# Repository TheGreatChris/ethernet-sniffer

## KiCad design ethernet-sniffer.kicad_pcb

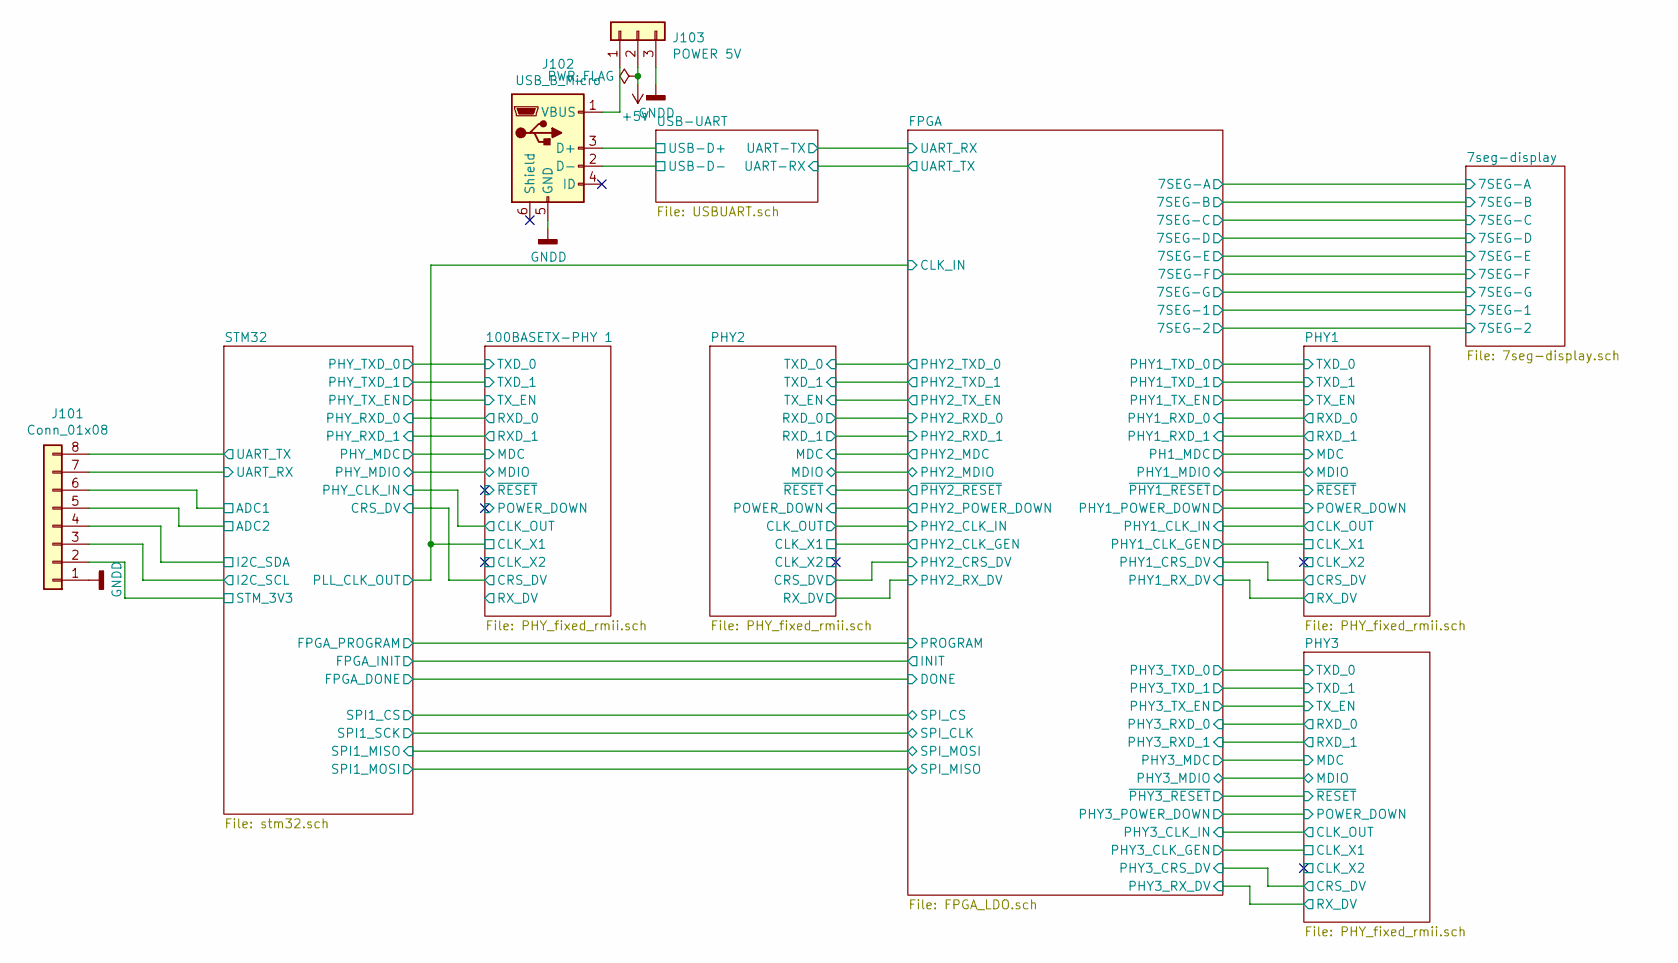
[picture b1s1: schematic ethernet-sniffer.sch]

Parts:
J101: Conn_01x08; PinHeader_1x08_P2.54mm_Vertical
J102: USB_B_Micro; USB_Micro-B_Amphenol_10103594-0001LF_Horizontal
J103: POWER 5V; PinHeader_1x03_P2.54mm_Vertical

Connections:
+5V: J103.2; also elsewhere on the board
/STM32/ADC1: J101.6; also elsewhere on the board
/STM32/ADC2: J101.5; also elsewhere on the board
/STM32/I2C_SCL: J101.3; also elsewhere on the board
/STM32/I2C_SDA: J101.4; also elsewhere on the board
/STM32/STM_3V3: J101.2; also elsewhere on the board
/STM32/UART_RX: J101.7; also elsewhere on the board
/STM32/UART_TX: J101.8; also elsewhere on the board
/USB-UART/USB-D+: J102.3 (D+); also elsewhere on the board
/USB-UART/USB-D-: J102.2 (D-); also elsewhere on the board
GNDD: J101.1, J102.5 (GND), J103.3; also elsewhere on the board
unnamed: J102.1 (VBUS), J103.1

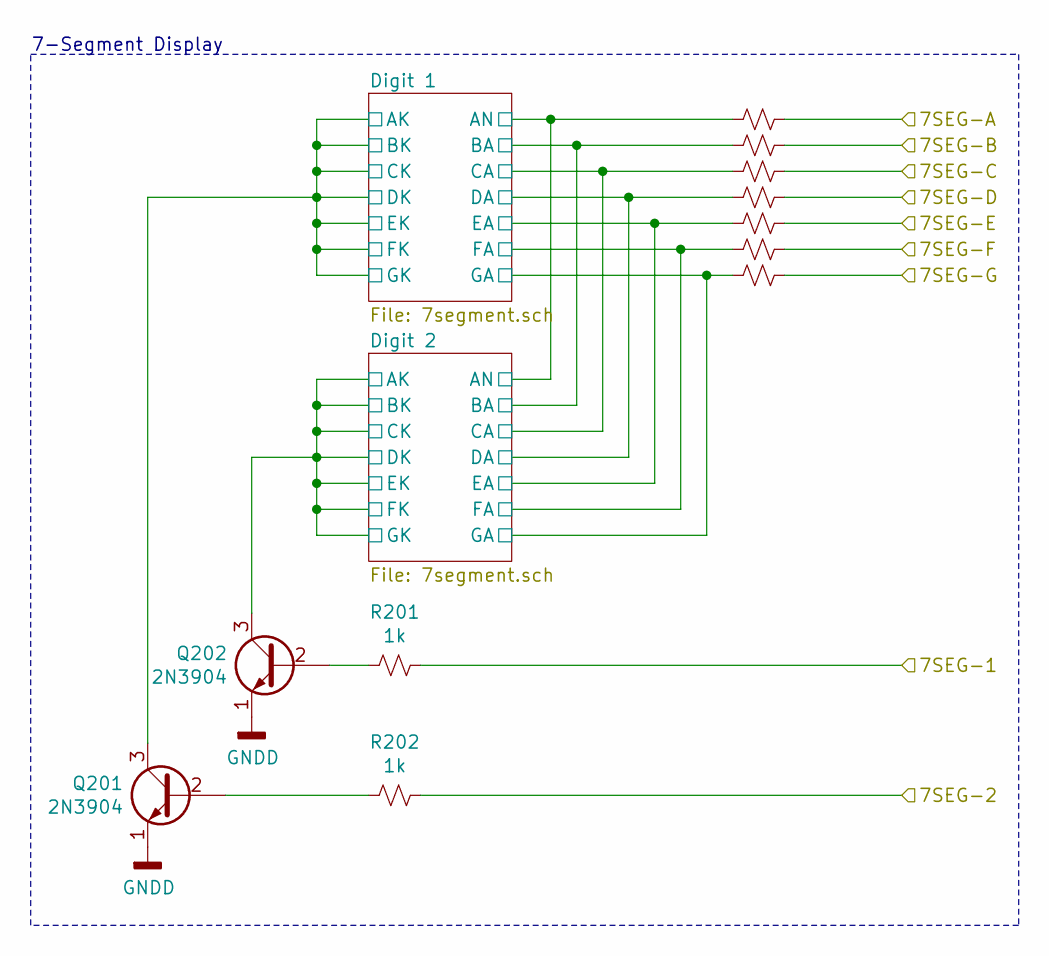
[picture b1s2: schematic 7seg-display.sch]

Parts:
Q201, Q202: 2N3904; SOT-23
R201, R202: 1k; R_0402_1005Metric
R203, R204, R205, R206, R207, R208, R209: 200; R_0402_1005Metric

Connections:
/7seg-display/7SEG-1: R201.1; also elsewhere on the board
/7seg-display/7SEG-2: R202.1; also elsewhere on the board
/7seg-display/7SEG-A: R203.1; also elsewhere on the board
/7seg-display/7SEG-B: R204.1; also elsewhere on the board
/7seg-display/7SEG-C: R205.1; also elsewhere on the board
/7seg-display/7SEG-D: R206.1; also elsewhere on the board
/7seg-display/7SEG-E: R207.1; also elsewhere on the board
/7seg-display/7SEG-F: R208.1; also elsewhere on the board
/7seg-display/7SEG-G: R209.1; also elsewhere on the board
/7seg-display/Digit 1/AK: Q201.3 (C); also elsewhere on the board
/7seg-display/Digit 1/AN: R203.2; also elsewhere on the board
/7seg-display/Digit 1/BA: R204.2; also elsewhere on the board
/7seg-display/Digit 1/CA: R205.2; also elsewhere on the board
/7seg-display/Digit 1/DA: R206.2; also elsewhere on the board
/7seg-display/Digit 1/EA: R207.2; also elsewhere on the board
/7seg-display/Digit 1/FA: R208.2; also elsewhere on the board
/7seg-display/Digit 1/GA: R209.2; also elsewhere on the board
/7seg-display/Digit 2/AK: Q202.3 (C); also elsewhere on the board
GNDD: Q201.1 (E), Q202.1 (E); also elsewhere on the board
unnamed: Q201.2 (B), R202.2
unnamed: Q202.2 (B), R201.2

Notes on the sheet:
7-Segment Display

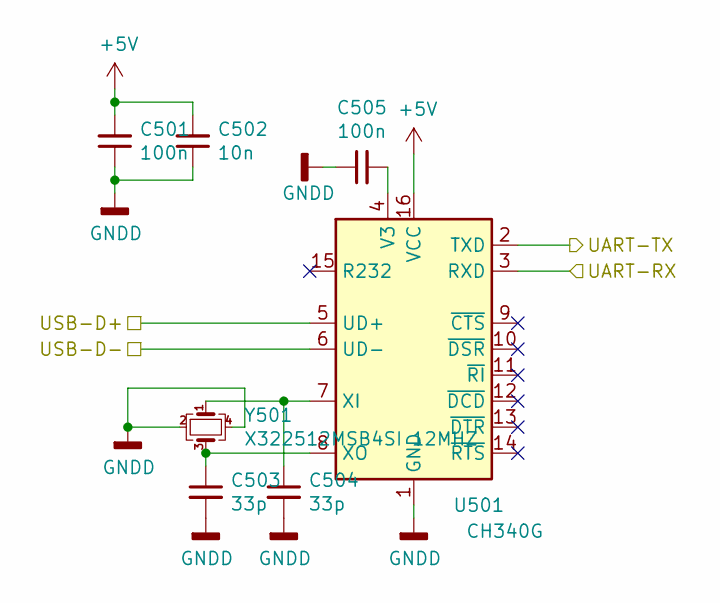
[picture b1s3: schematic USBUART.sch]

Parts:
C501, C505: 100n; C_0402_1005Metric
C502: 10n; C_0402_1005Metric
C503, C504: 33p; C_0402_1005Metric
U501: CH340G; SOIC-16_3.9x9.9mm_P1.27mm
Y501: X322512MSB4SI 12MHZ; Crystal_SMD_3225-4Pin_3.2x2.5mm

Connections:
+5V: C501.2, C502.2, U501.16 (VCC); also elsewhere on the board
/USB-UART/UART-RX: U501.3 (RXD); also elsewhere on the board
/USB-UART/UART-TX: U501.2 (TXD); also elsewhere on the board
/USB-UART/USB-D+: U501.5 (UD+); also elsewhere on the board
/USB-UART/USB-D-: U501.6 (UD-); also elsewhere on the board
GNDD: C501.1, C502.1, C503.2, C504.2, C505.1, U501.1 (GND), Y501.2, Y501.4; also elsewhere on the board
unnamed: C503.1, U501.8 (XO), Y501.3
unnamed: C504.1, U501.7 (XI), Y501.1
unnamed: C505.2, U501.4 (V3)

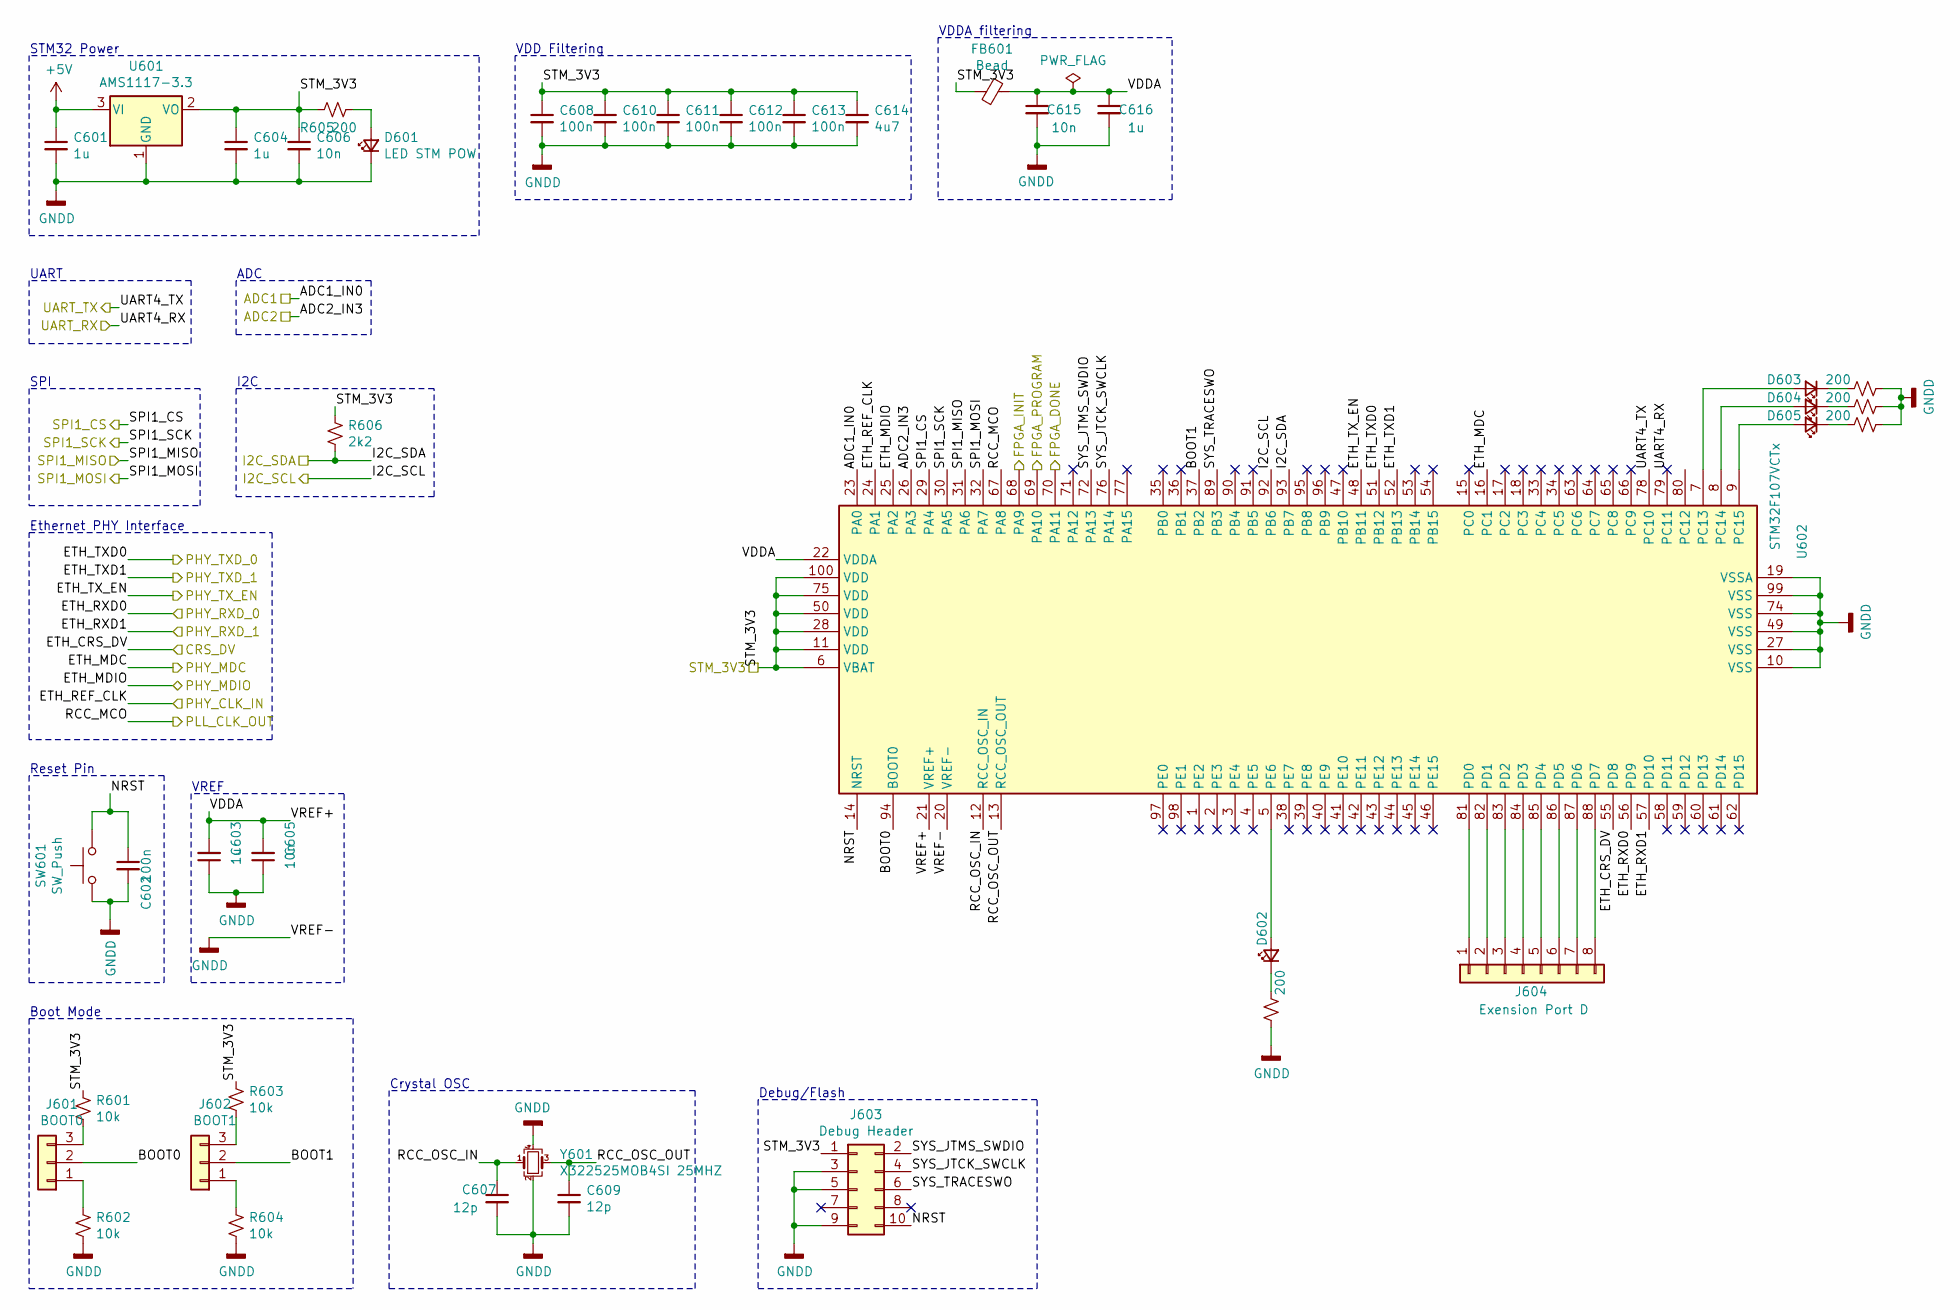
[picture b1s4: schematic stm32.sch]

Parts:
C601, C603, C604, C616: 1u; C_0402_1005Metric
C602, C608, C610, C611, C612, C613: 100n; C_0402_1005Metric
C605, C606, C615: 10n; C_0402_1005Metric
C607, C609: 12p; C_0402_1005Metric
C614: 4u7; C_0402_1005Metric
D601: LED STM POW; LED_0603_1608Metric
D602, D603, D604, D605: LED_Small; LED_0603_1608Metric
FB601: Bead; L_0805_2012Metric
J601: BOOT0; PinHeader_1x03_P2.54mm_Vertical
J602: BOOT1; PinHeader_1x03_P2.54mm_Vertical
J603: Debug Header; PinHeader_2x05_P2.54mm_Vertical
J604: Exension Port D; PinHeader_1x08_P2.54mm_Vertical
R601, R602, R603, R604: 10k; R_0402_1005Metric
R605, R607, R608, R609, R610: 200; R_0402_1005Metric
R606: 2k2; R_0402_1005Metric
SW601: SW_Push; SW_Push_SPST_NO_Alps_SKRK
U601: AMS1117-3.3; SOT-223-3_TabPin2
U602: STM32F107VCTx; LQFP-100_14x14mm_P0.5mm
Y601: X322525MOB4SI 25MHZ; Crystal_SMD_3225-4Pin_3.2x2.5mm

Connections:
+5V: C601.1, U601.3 (VI); also elsewhere on the board
/100BASETX-PHY 1/CLK_OUT: U602.24 (PA1); also elsewhere on the board
/100BASETX-PHY 1/CRS_DV: U602.55 (PD8); also elsewhere on the board
/100BASETX-PHY 1/MDC: U602.16 (PC1); also elsewhere on the board
/100BASETX-PHY 1/MDIO: U602.25 (PA2); also elsewhere on the board
/FPGA/CLK_IN: U602.67 (PA8); also elsewhere on the board
/FPGA/DONE: U602.70 (PA11); also elsewhere on the board
/STM32/ADC1: U602.23 (PA0); also elsewhere on the board
/STM32/ADC2: U602.26 (PA3); also elsewhere on the board
/STM32/BOOT0: J601.2, U602.94 (BOOT0)
/STM32/BOOT1: J602.2, U602.37 (PB2)
/STM32/FPGA_INIT: U602.68 (PA9); also elsewhere on the board
/STM32/FPGA_PROGRAM: U602.69 (PA10); also elsewhere on the board
/STM32/I2C_SCL: U602.92 (PB6); also elsewhere on the board
/STM32/I2C_SDA: R606.2, U602.93 (PB7); also elsewhere on the board
/STM32/NRST: C602.1, J603.10, SW601.2, U602.14 (NRST)
/STM32/PHY_RXD_0: U602.56 (PD9); also elsewhere on the board
/STM32/PHY_RXD_1: U602.57 (PD10); also elsewhere on the board
/STM32/PHY_TXD_0: U602.51 (PB12); also elsewhere on the board
/STM32/PHY_TXD_1: U602.52 (PB13); also elsewhere on the board
/STM32/PHY_TX_EN: U602.48 (PB11); also elsewhere on the board
/STM32/RCC_OSC_IN: C607.1, U602.12 (RCC_OSC_IN), Y601.1
/STM32/RCC_OSC_OUT: C609.1, U602.13 (RCC_OSC_OUT), Y601.3
/STM32/SPI1_CS: U602.29 (PA4); also elsewhere on the board
/STM32/SPI1_MISO: U602.31 (PA6); also elsewhere on the board
/STM32/SPI1_MOSI: U602.32 (PA7); also elsewhere on the board
/STM32/SPI1_SCK: U602.30 (PA5); also elsewhere on the board
/STM32/STM_3V3: C604.1, C606.1, C608.1, C610.1, C611.1, C612.1, C613.1, C614.1, FB601.2, J603.1, R601.1, R603.1, R605.1, R606.1, U601.2 (VO), U602.6 (VBAT), U602.11 (VDD), U602.28 (VDD), U602.50 (VDD), U602.75 (VDD), U602.100 (VDD); also elsewhere on the board
/STM32/SYS_JTCK_SWCLK: J603.4, U602.76 (PA14)
/STM32/SYS_JTMS_SWDIO: J603.2, U602.72 (PA13)
/STM32/SYS_TRACESWO: J603.6, U602.89 (PB3)
/STM32/UART_RX: U602.79 (PC11); also elsewhere on the board
/STM32/UART_TX: U602.78 (PC10); also elsewhere on the board
/STM32/VDDA: C603.2, C605.2, C615.1, C616.1, FB601.1, U602.21 (VREF+), U602.22 (VDDA)
GNDD: C601.2, C602.2, C603.1, C604.2, C605.1, C606.2, C607.2, C608.2, C609.2, C610.2, C611.2, C612.2, C613.2, C614.2, C615.2, C616.2, D601.1 (K), J603.3, J603.5, J603.9, R602.2, R604.2, R607.1, R608.1, R609.1, R610.1, SW601.1, U601.1 (GND), U602.10 (VSS), U602.19 (VSSA), U602.20 (VREF-), U602.27 (VSS), U602.49 (VSS), U602.74 (VSS), U602.99 (VSS), Y601.2, Y601.4; also elsewhere on the board
unnamed: D601.2 (A), R605.2
unnamed: D602.1 (K), R607.2
unnamed: D602.2 (A), U602.5 (PE6)
unnamed: D603.1 (K), R608.2
unnamed: D603.2 (A), U602.7 (PC13)
unnamed: D604.1 (K), R609.2
unnamed: D604.2 (A), U602.8 (PC14)
unnamed: D605.1 (K), R610.2
unnamed: D605.2 (A), U602.9 (PC15)
unnamed: J601.1, R602.1
unnamed: J601.3, R601.2
unnamed: J602.1, R604.1
unnamed: J602.3, R603.2
unnamed: J604.1, U602.81 (PD0)
unnamed: J604.2, U602.82 (PD1)
unnamed: J604.3, U602.83 (PD2)
unnamed: J604.4, U602.84 (PD3)
unnamed: J604.5, U602.85 (PD4)
unnamed: J604.6, U602.86 (PD5)
unnamed: J604.7, U602.87 (PD6)
unnamed: J604.8, U602.88 (PD7)

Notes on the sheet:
Reset Pin
Boot Mode
VREF
Crystal OSC
Debug/Flash
Ethernet PHY Interface
SPI
STM32 Power
VDD Filtering
UART
ADC
VDDA filtering
I2C

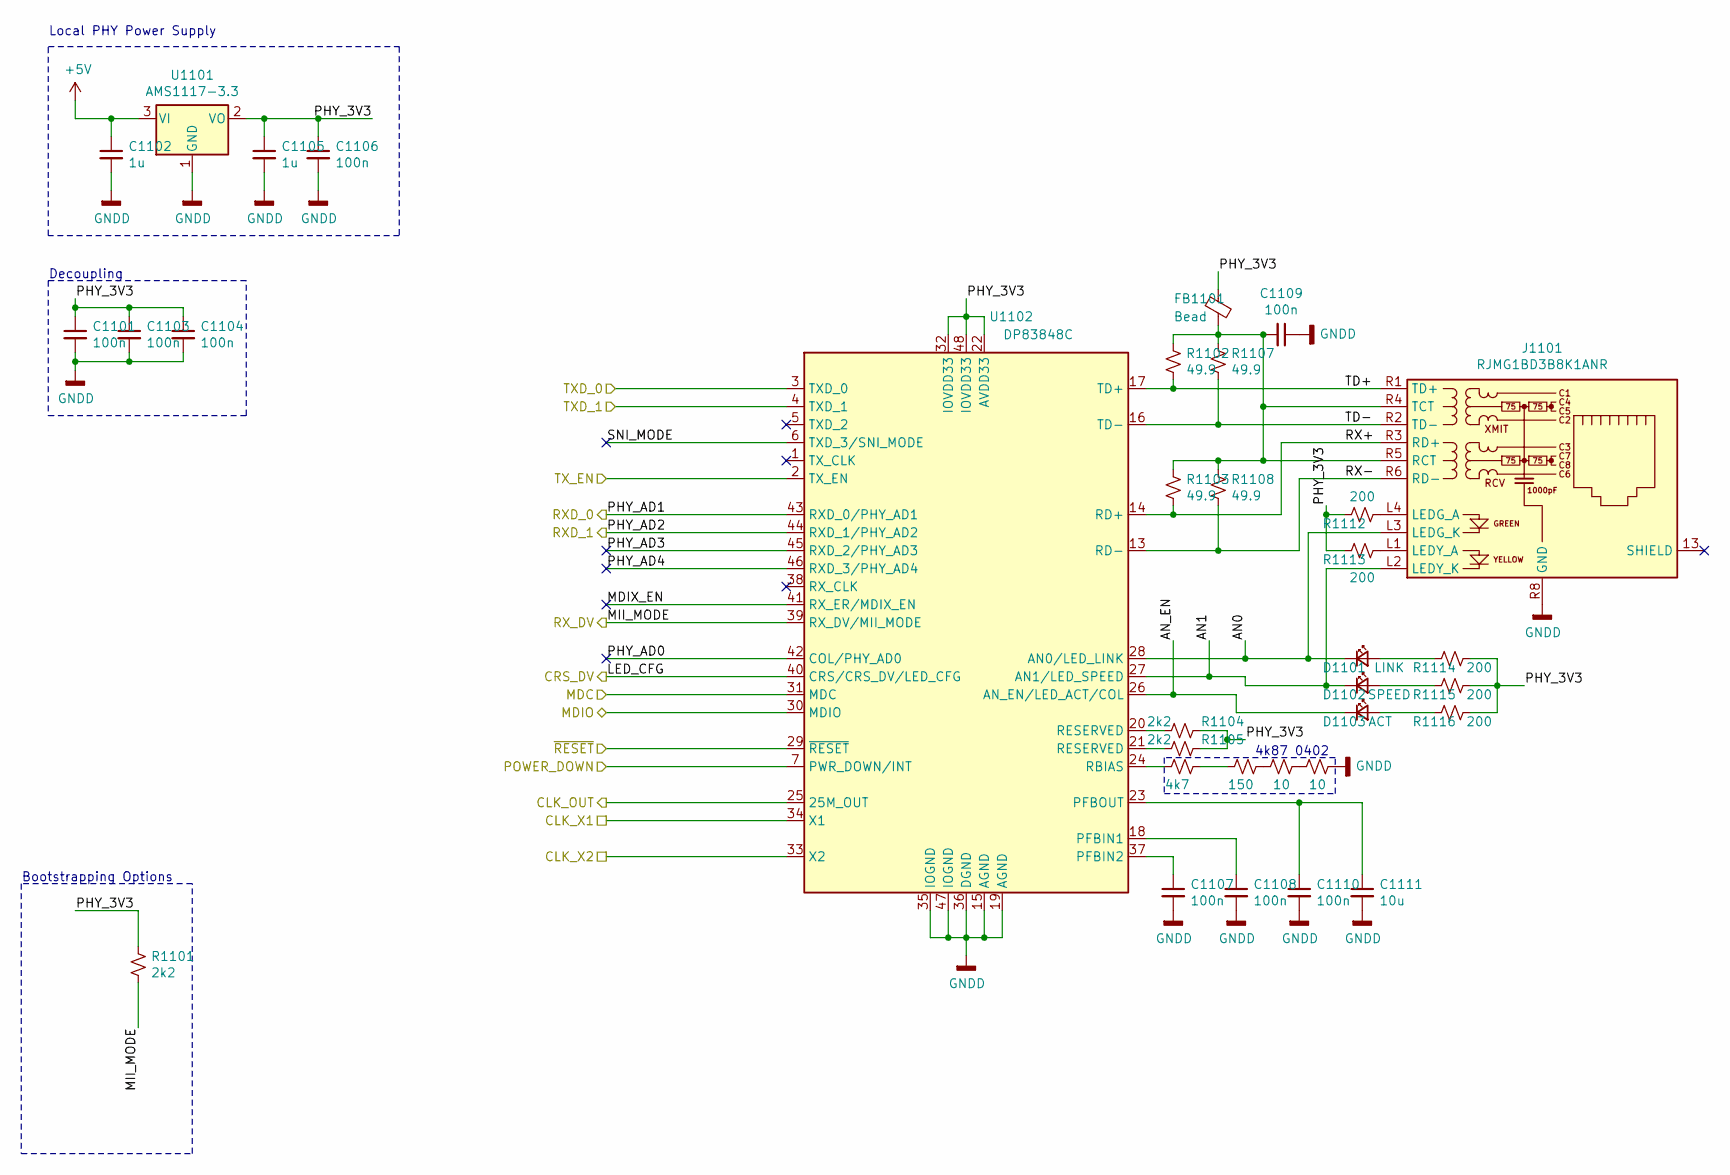
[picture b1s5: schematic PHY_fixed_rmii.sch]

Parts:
C702, C705: 1u; C_0402_1005Metric
C706, C707, C708, C709, C710, C1001, C1003, C1004: 100n; C_0402_1005Metric
C711: 10u; C_0402_1005Metric
D701: LINK; LED_0603_1608Metric
D702: SPEED; LED_0603_1608Metric
D703: ACT; LED_0603_1608Metric
FB701: Bead; L_0805_2012Metric
J701: RJMG1BD3B8K1ANR; RJ45_Amphenol_RJMG1BD3B8K1ANR
R701, R704, R705: 2k2; R_0402_1005Metric
R702, R703, R707, R708: 49.9; R_0402_1005Metric
R706: 4k7; R_0402_1005Metric
R709: 150; R_0402_1005Metric
R710, R711: 10; R_0402_1005Metric
R712, R713, R714, R715, R716: 200; R_0402_1005Metric
U701: AMS1117-3.3; SOT-223-3_TabPin2
U702: DP83848C; LQFP-48_7x7mm_P0.5mm

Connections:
+5V: C702.1, U701.3 (VI); also elsewhere on the board
/100BASETX-PHY 1/AN0: D701.1 (K), J701.L3 (LEDG_K), U702.28 (AN0/LED_LINK)
/100BASETX-PHY 1/AN1: D702.1 (K), J701.L2 (LEDY_K), U702.27 (AN1/LED_SPEED)
/100BASETX-PHY 1/AN_EN: D703.1 (K), U702.26 (AN_EN/LED_ACT/COL)
/100BASETX-PHY 1/CLK_OUT: U702.25 (25M_OUT); also elsewhere on the board
/100BASETX-PHY 1/CLK_X2: U702.33 (X2)
/100BASETX-PHY 1/CRS_DV: U702.40 (CRS/CRS_DV/LED_CFG); also elsewhere on the board
/100BASETX-PHY 1/MDC: U702.31 (MDC); also elsewhere on the board
/100BASETX-PHY 1/MDIO: U702.30 (MDIO); also elsewhere on the board
/100BASETX-PHY 1/MDIX_EN: U702.41 (RX_ER/MDIX_EN)
/100BASETX-PHY 1/PHY_AD0: U702.42 (COL/PHY_AD0)
/100BASETX-PHY 1/PHY_AD3: U702.45 (RXD_2/PHY_AD3)
/100BASETX-PHY 1/PHY_AD4: U702.46 (RXD_3/PHY_AD4)
/100BASETX-PHY 1/POWER_DOWN: U702.7 (PWR_DOWN/INT)
/100BASETX-PHY 1/RX+: J701.R3 (RD+), R703.2, U702.14 (RD+)
/100BASETX-PHY 1/RX-: J701.R6 (RD-), R708.2, U702.13 (RD-)
/100BASETX-PHY 1/RX_DV: R701.2, U702.39 (RX_DV/MII_MODE)
/100BASETX-PHY 1/SNI_MODE: U702.6 (TXD_3/SNI_MODE)
/100BASETX-PHY 1/TD+: J701.R1 (TD+), R702.2, U702.17 (TD+)
/100BASETX-PHY 1/TD-: J701.R2 (TD-), R707.2, U702.16 (TD-)
/100BASETX-PHY 1/~RESET: U702.29 (~RESET~)
/FPGA/CLK_IN: U702.34 (X1); also elsewhere on the board
/STM32/PHY_RXD_0: U702.43 (RXD_0/PHY_AD1); also elsewhere on the board
/STM32/PHY_RXD_1: U702.44 (RXD_1/PHY_AD2); also elsewhere on the board
/STM32/PHY_TXD_0: U702.3 (TXD_0); also elsewhere on the board
/STM32/PHY_TXD_1: U702.4 (TXD_1); also elsewhere on the board
/STM32/PHY_TX_EN: U702.2 (TX_EN); also elsewhere on the board
GNDD: C702.2, C705.2, C706.2, C707.2, C708.2, C709.1, C710.2, C711.2, C1001.2, C1003.2, C1004.2, J701.R8 (GND), R711.1, U701.1 (GND), U702.15 (AGND), U702.19 (AGND), U702.35 (IOGND), U702.36 (DGND), U702.47 (IOGND); also elsewhere on the board
unnamed: C707.1, U702.37 (PFBIN2)
unnamed: C708.1, U702.18 (PFBIN1)
unnamed: C709.2, FB701.2, J701.R4 (TCT), J701.R5 (RCT), R702.1, R703.1, R707.1, R708.1
unnamed: C710.1, C711.1, U702.23 (PFBOUT)
unnamed: D701.2 (A), R714.2
unnamed: D702.2 (A), R715.2
unnamed: D703.2 (A), R716.2
unnamed: J701.L1 (LEDY_A), R713.1
unnamed: J701.L4 (LEDG_A), R712.1
unnamed: R704.2, U702.20 (RESERVED)
unnamed: R705.2, U702.21 (RESERVED)
unnamed: R706.1, R709.2
unnamed: R706.2, U702.24 (RBIAS)
unnamed: R709.1, R710.2
unnamed: R710.1, R711.2

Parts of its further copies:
C701, C703, C704, C801, C803, C804, C806, C807, C808, C809, C810, C1006, C1007, C1008, C1009, C1010, C1101, C1103, C1104, C1106, C1107, C1108, C1109, C1110: 100n; C_0402_1005Metric
C802, C805, C1002, C1005, C1102, C1105: 1u; C_0402_1005Metric
C811, C1011, C1111: 10u; C_0402_1005Metric
D801, D1001, D1101: LINK; LED_0603_1608Metric
D802, D1002, D1102: SPEED; LED_0603_1608Metric
D803, D1003, D1103: ACT; LED_0603_1608Metric
FB801, FB1001, FB1101: Bead; L_0805_2012Metric
J801, J1001, J1101: RJMG1BD3B8K1ANR; RJ45_Amphenol_RJMG1BD3B8K1ANR
R801, R804, R805, R1001, R1004, R1005, R1101, R1104, R1105: 2k2; R_0402_1005Metric
R802, R803, R807, R808, R1002, R1003, R1007, R1008, R1102, R1103, R1107, R1108: 49.9; R_0402_1005Metric
R806, R1006, R1106: 4k7; R_0402_1005Metric
R809, R1009, R1109: 150; R_0402_1005Metric
R810, R811, R1010, R1011, R1110, R1111: 10; R_0402_1005Metric
R812, R813, R814, R815, R816, R1012, R1013, R1014, R1015, R1016, R1112, R1113, R1114, R1115, R1116: 200; R_0402_1005Metric
U801, U1001, U1101: AMS1117-3.3; SOT-223-3_TabPin2
U802, U1002, U1102: DP83848C; LQFP-48_7x7mm_P0.5mm

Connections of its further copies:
+5V: C802.1, C1002.1, C1102.1, U801.3 (VI), U1001.3 (VI), U1101.3 (VI); also elsewhere on the board
/FPGA/PHY1_POWER_DOWN: U1102.7 (PWR_DOWN/INT); also elsewhere on the board
/FPGA/PHY1_RXD_0: U1102.43 (RXD_0/PHY_AD1); also elsewhere on the board
/FPGA/PHY1_RXD_1: U1102.44 (RXD_1/PHY_AD2); also elsewhere on the board
/FPGA/PHY1_RX_DV: R1101.2, U1102.39 (RX_DV/MII_MODE); also elsewhere on the board
/FPGA/PHY1_TXD_0: U1102.3 (TXD_0); also elsewhere on the board
/FPGA/PHY1_TXD_1: U1102.4 (TXD_1); also elsewhere on the board
/FPGA/PHY1_TX_EN: U1102.2 (TX_EN); also elsewhere on the board
/FPGA/PHY2_POWER_DOWN: U1002.7 (PWR_DOWN/INT); also elsewhere on the board
/FPGA/PHY2_RXD_0: U1002.43 (RXD_0/PHY_AD1); also elsewhere on the board
/FPGA/PHY2_RXD_1: U1002.44 (RXD_1/PHY_AD2); also elsewhere on the board
/FPGA/PHY2_RX_DV: R1001.2, U1002.39 (RX_DV/MII_MODE); also elsewhere on the board
/FPGA/PHY2_TXD_0: U1002.3 (TXD_0); also elsewhere on the board
/FPGA/PHY2_TXD_1: U1002.4 (TXD_1); also elsewhere on the board
/FPGA/PHY2_TX_EN: U1002.2 (TX_EN); also elsewhere on the board
/FPGA/PHY3_POWER_DOWN: U802.7 (PWR_DOWN/INT); also elsewhere on the board
/FPGA/PHY3_RXD_0: U802.43 (RXD_0/PHY_AD1); also elsewhere on the board
/FPGA/PHY3_RXD_1: U802.44 (RXD_1/PHY_AD2); also elsewhere on the board
/FPGA/PHY3_RX_DV: R801.2, U802.39 (RX_DV/MII_MODE); also elsewhere on the board
/FPGA/PHY3_TXD_0: U802.3 (TXD_0); also elsewhere on the board
/FPGA/PHY3_TXD_1: U802.4 (TXD_1); also elsewhere on the board
/FPGA/PHY3_TX_EN: U802.2 (TX_EN); also elsewhere on the board
/FPGA/~PHY1_RESET: U1102.29 (~RESET~); also elsewhere on the board
/FPGA/~PHY2_RESET: U1002.29 (~RESET~); also elsewhere on the board
/FPGA/~PHY3_RESET: U802.29 (~RESET~); also elsewhere on the board
/PHY1/AN0: D1101.1 (K), J1101.L3 (LEDG_K), U1102.28 (AN0/LED_LINK)
/PHY1/AN1: D1102.1 (K), J1101.L2 (LEDY_K), U1102.27 (AN1/LED_SPEED)
/PHY1/AN_EN: D1103.1 (K), U1102.26 (AN_EN/LED_ACT/COL)
/PHY1/CLK_OUT: U1102.25 (25M_OUT); also elsewhere on the board
/PHY1/CLK_X1: U1102.34 (X1); also elsewhere on the board
/PHY1/CLK_X2: U1102.33 (X2)
/PHY1/CRS_DV: U1102.40 (CRS/CRS_DV/LED_CFG); also elsewhere on the board
/PHY1/MDC: U1102.31 (MDC); also elsewhere on the board
/PHY1/MDIO: U1102.30 (MDIO); also elsewhere on the board
/PHY1/MDIX_EN: U1102.41 (RX_ER/MDIX_EN)
/PHY1/PHY_3V3: C1101.1, C1103.1, C1104.1, C1105.1, C1106.1, FB1101.1, R1101.1, R1104.1, R1105.1, R1112.2, R1113.2, R1114.1, R1115.1, R1116.1, U1101.2 (VO), U1102.22 (AVDD33), U1102.32 (IOVDD33), U1102.48 (IOVDD33)
/PHY1/PHY_AD0: U1102.42 (COL/PHY_AD0)
/PHY1/PHY_AD3: U1102.45 (RXD_2/PHY_AD3)
/PHY1/PHY_AD4: U1102.46 (RXD_3/PHY_AD4)
/PHY1/RX+: J1101.R3 (RD+), R1103.2, U1102.14 (RD+)
/PHY1/RX-: J1101.R6 (RD-), R1108.2, U1102.13 (RD-)
/PHY1/SNI_MODE: U1102.6 (TXD_3/SNI_MODE)
/PHY1/TD+: J1101.R1 (TD+), R1102.2, U1102.17 (TD+)
/PHY1/TD-: J1101.R2 (TD-), R1107.2, U1102.16 (TD-)
/PHY2/AN0: D1001.1 (K), J1001.L3 (LEDG_K), U1002.28 (AN0/LED_LINK)
/PHY2/AN1: D1002.1 (K), J1001.L2 (LEDY_K), U1002.27 (AN1/LED_SPEED)
/PHY2/AN_EN: D1003.1 (K), U1002.26 (AN_EN/LED_ACT/COL)
/PHY2/CLK_OUT: U1002.25 (25M_OUT); also elsewhere on the board
/PHY2/CLK_X1: U1002.34 (X1); also elsewhere on the board
/PHY2/CLK_X2: U1002.33 (X2)
/PHY2/CRS_DV: U1002.40 (CRS/CRS_DV/LED_CFG); also elsewhere on the board
/PHY2/MDC: U1002.31 (MDC); also elsewhere on the board
/PHY2/MDIO: U1002.30 (MDIO); also elsewhere on the board
/PHY2/MDIX_EN: U1002.41 (RX_ER/MDIX_EN)
/PHY2/PHY_AD0: U1002.42 (COL/PHY_AD0)
/PHY2/PHY_AD3: U1002.45 (RXD_2/PHY_AD3)
/PHY2/PHY_AD4: U1002.46 (RXD_3/PHY_AD4)
/PHY2/RX+: J1001.R3 (RD+), R1003.2, U1002.14 (RD+)
/PHY2/RX-: J1001.R6 (RD-), R1008.2, U1002.13 (RD-)
/PHY2/SNI_MODE: U1002.6 (TXD_3/SNI_MODE)
/PHY2/TD+: J1001.R1 (TD+), R1002.2, U1002.17 (TD+)
/PHY2/TD-: J1001.R2 (TD-), R1007.2, U1002.16 (TD-)
/PHY3/AN0: D801.1 (K), J801.L3 (LEDG_K), U802.28 (AN0/LED_LINK)
/PHY3/AN1: D802.1 (K), J801.L2 (LEDY_K), U802.27 (AN1/LED_SPEED)
/PHY3/AN_EN: D803.1 (K), U802.26 (AN_EN/LED_ACT/COL)
/PHY3/CLK_OUT: U802.25 (25M_OUT); also elsewhere on the board
/PHY3/CLK_X1: U802.34 (X1); also elsewhere on the board
/PHY3/CLK_X2: U802.33 (X2)
/PHY3/CRS_DV: U802.40 (CRS/CRS_DV/LED_CFG); also elsewhere on the board
/PHY3/MDC: U802.31 (MDC); also elsewhere on the board
/PHY3/MDIO: U802.30 (MDIO); also elsewhere on the board
/PHY3/MDIX_EN: U802.41 (RX_ER/MDIX_EN)
/PHY3/PHY_3V3: C801.1, C803.1, C804.1, C805.1, C806.1, FB801.1, R801.1, R804.1, R805.1, R812.2, R813.2, R814.1, R815.1, R816.1, U801.2 (VO), U802.22 (AVDD33), U802.32 (IOVDD33), U802.48 (IOVDD33)
/PHY3/PHY_AD0: U802.42 (COL/PHY_AD0)
/PHY3/PHY_AD3: U802.45 (RXD_2/PHY_AD3)
/PHY3/PHY_AD4: U802.46 (RXD_3/PHY_AD4)
/PHY3/RX+: J801.R3 (RD+), R803.2, U802.14 (RD+)
/PHY3/RX-: J801.R6 (RD-), R808.2, U802.13 (RD-)
/PHY3/SNI_MODE: U802.6 (TXD_3/SNI_MODE)
/PHY3/TD+: J801.R1 (TD+), R802.2, U802.17 (TD+)
/PHY3/TD-: J801.R2 (TD-), R807.2, U802.16 (TD-)
GNDD: C701.2, C703.2, C704.2, C801.2, C802.2, C803.2, C804.2, C805.2, C806.2, C807.2, C808.2, C809.1, C810.2, C811.2, C1002.2, C1005.2, C1006.2, C1007.2, C1008.2, C1009.1, C1010.2, C1011.2, C1101.2, C1102.2, C1103.2, C1104.2, C1105.2, C1106.2, C1107.2, C1108.2, C1109.1, C1110.2, C1111.2, J801.R8 (GND), J1001.R8 (GND), J1101.R8 (GND), R811.1, R1011.1, R1111.1, U801.1 (GND), U802.15 (AGND), U802.19 (AGND), U802.35 (IOGND), U802.36 (DGND), U802.47 (IOGND), U1001.1 (GND), U1002.15 (AGND), U1002.19 (AGND), U1002.35 (IOGND), U1002.36 (DGND), U1002.47 (IOGND), U1101.1 (GND), U1102.15 (AGND), U1102.19 (AGND), U1102.35 (IOGND), U1102.36 (DGND), U1102.47 (IOGND); also elsewhere on the board
unnamed: C807.1, U802.37 (PFBIN2)
unnamed: C808.1, U802.18 (PFBIN1)
unnamed: C809.2, FB801.2, J801.R4 (TCT), J801.R5 (RCT), R802.1, R803.1, R807.1, R808.1
unnamed: C810.1, C811.1, U802.23 (PFBOUT)
unnamed: C1007.1, U1002.37 (PFBIN2)
unnamed: C1008.1, U1002.18 (PFBIN1)
unnamed: C1009.2, FB1001.2, J1001.R4 (TCT), J1001.R5 (RCT), R1002.1, R1003.1, R1007.1, R1008.1
unnamed: C1010.1, C1011.1, U1002.23 (PFBOUT)
unnamed: C1107.1, U1102.37 (PFBIN2)
unnamed: C1108.1, U1102.18 (PFBIN1)
unnamed: C1109.2, FB1101.2, J1101.R4 (TCT), J1101.R5 (RCT), R1102.1, R1103.1, R1107.1, R1108.1
unnamed: C1110.1, C1111.1, U1102.23 (PFBOUT)
unnamed: D801.2 (A), R814.2
unnamed: D802.2 (A), R815.2
unnamed: D803.2 (A), R816.2
unnamed: D1001.2 (A), R1014.2
unnamed: D1002.2 (A), R1015.2
unnamed: D1003.2 (A), R1016.2
unnamed: D1101.2 (A), R1114.2
unnamed: D1102.2 (A), R1115.2
unnamed: D1103.2 (A), R1116.2
unnamed: J801.L1 (LEDY_A), R813.1
unnamed: J801.L4 (LEDG_A), R812.1
unnamed: J1001.L1 (LEDY_A), R1013.1
unnamed: J1001.L4 (LEDG_A), R1012.1
unnamed: J1101.L1 (LEDY_A), R1113.1
unnamed: J1101.L4 (LEDG_A), R1112.1
unnamed: R804.2, U802.20 (RESERVED)
unnamed: R805.2, U802.21 (RESERVED)
unnamed: R806.1, R809.2
unnamed: R806.2, U802.24 (RBIAS)
unnamed: R809.1, R810.2
unnamed: R810.1, R811.2
unnamed: R1004.2, U1002.20 (RESERVED)
unnamed: R1005.2, U1002.21 (RESERVED)
unnamed: R1006.1, R1009.2
unnamed: R1006.2, U1002.24 (RBIAS)
unnamed: R1009.1, R1010.2
unnamed: R1010.1, R1011.2
unnamed: R1104.2, U1102.20 (RESERVED)
unnamed: R1105.2, U1102.21 (RESERVED)
unnamed: R1106.1, R1109.2
unnamed: R1106.2, U1102.24 (RBIAS)
unnamed: R1109.1, R1110.2
unnamed: R1110.1, R1111.2

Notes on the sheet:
Bootstrapping Options
Local PHY Power Supply
Decoupling
4k87 0402
